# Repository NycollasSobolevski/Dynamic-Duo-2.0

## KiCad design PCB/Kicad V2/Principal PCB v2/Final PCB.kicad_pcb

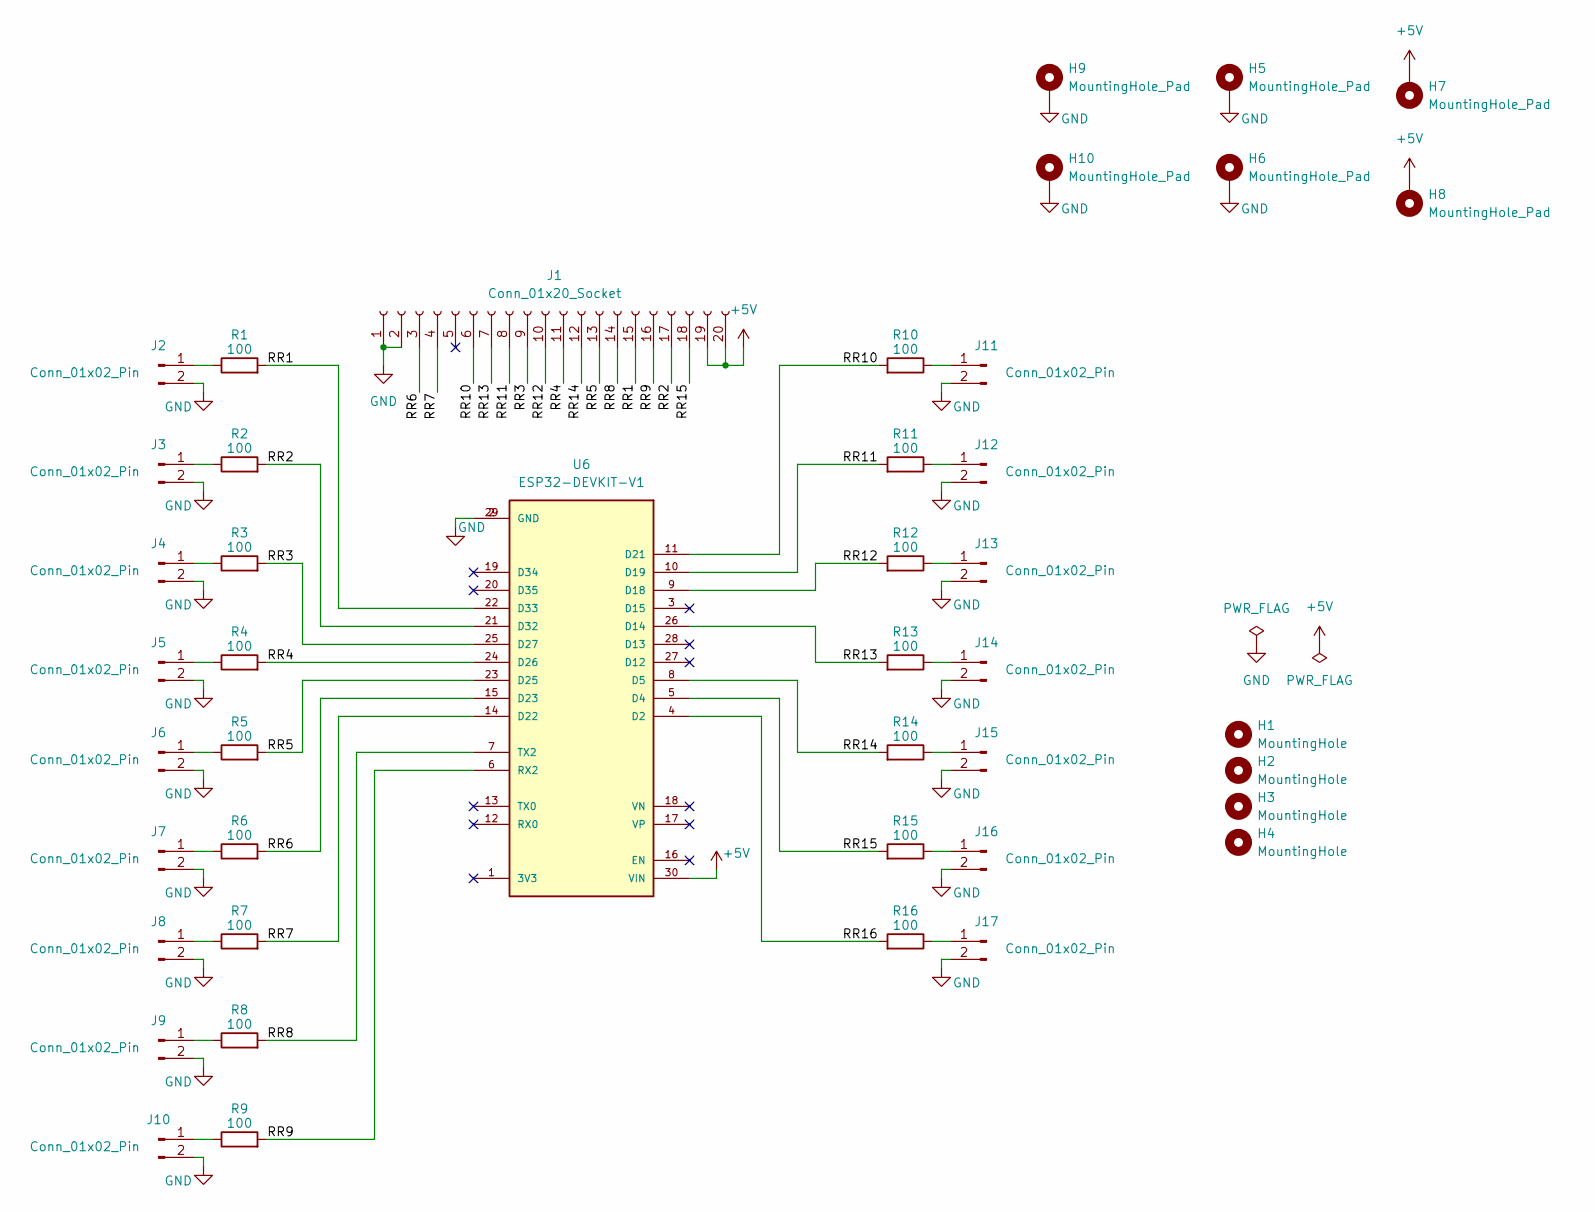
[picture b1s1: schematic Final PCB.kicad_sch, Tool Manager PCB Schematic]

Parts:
H1, H2, H3, H4: MountingHole; MountingHole_3.2mm_M3
H5, H6, H7, H8, H9, H10: MountingHole_Pad; DefaultVia
J1: Conn_01x20_Socket; PinSocket_2x10_P2.54mm_VerticalLongPads
J2, J3, J4, J5, J6, J7, J8, J9, J10, J11, J12, J13, J14, J15, J16, J17: Conn_01x02_Pin; PinHeader_1x02_P2.54mm_VerticalLongPads
R1, R2, R3, R4, R5, R6, R7, R8, R9, R10, R11, R12, R13, R14, R15, R16: 100; R_Axial_DIN0411_L9.9mm_D3.6mm_P12.70mm_HorizontalLONGPADS
U6: ESP32-DEVKIT-V1; MODULE_ESP32_DEVKIT_V1LongPads; PARTREV N/A

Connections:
+5V: H7.1, H8.1, J1.19, J1.20, U6.30 (VIN)
/RR1: J1.15, R1.2, U6.22 (D33)
/RR2: J1.17, R2.2, U6.21 (D32)
/RR3: J1.9, R3.2, U6.25 (D27)
/RR4: J1.11, R4.2, U6.24 (D26)
/RR5: J1.13, R5.2, U6.23 (D25)
/RR6: J1.3, R6.2, U6.15 (D23)
/RR7: J1.4, R7.2, U6.14 (D22)
/RR8: J1.14, R8.2, U6.7 (TX2)
/RR9: J1.16, R9.2, U6.6 (RX2)
/RR10: J1.6, R10.2, U6.11 (D21)
/RR11: J1.8, R11.2, U6.10 (D19)
/RR12: J1.10, R12.2, U6.9 (D18)
/RR13: J1.7, R13.2, U6.26 (D14)
/RR14: J1.12, R14.2, U6.8 (D5)
/RR15: J1.18, R15.2, U6.5 (D4)
/RR16: R16.2, U6.4 (D2)
GND: H5.1, H6.1, H9.1, H10.1, J1.1, J1.2, J2.2, J3.2, J4.2, J5.2, J6.2, J7.2, J8.2, J9.2, J10.2, J11.2, J12.2, J13.2, J14.2, J15.2, J16.2, J17.2, U6.2 (GND), U6.29 (GND)
unnamed: J2.1, R1.1
unnamed: J3.1, R2.1
unnamed: J4.1, R3.1
unnamed: J5.1, R4.1
unnamed: J6.1, R5.1
unnamed: J7.1, R6.1
unnamed: J8.1, R7.1
unnamed: J9.1, R8.1
unnamed: J10.1, R9.1
unnamed: J11.1, R10.1
unnamed: J12.1, R11.1
unnamed: J13.1, R12.1
unnamed: J14.1, R13.1
unnamed: J15.1, R14.1
unnamed: J16.1, R15.1
unnamed: J17.1, R16.1

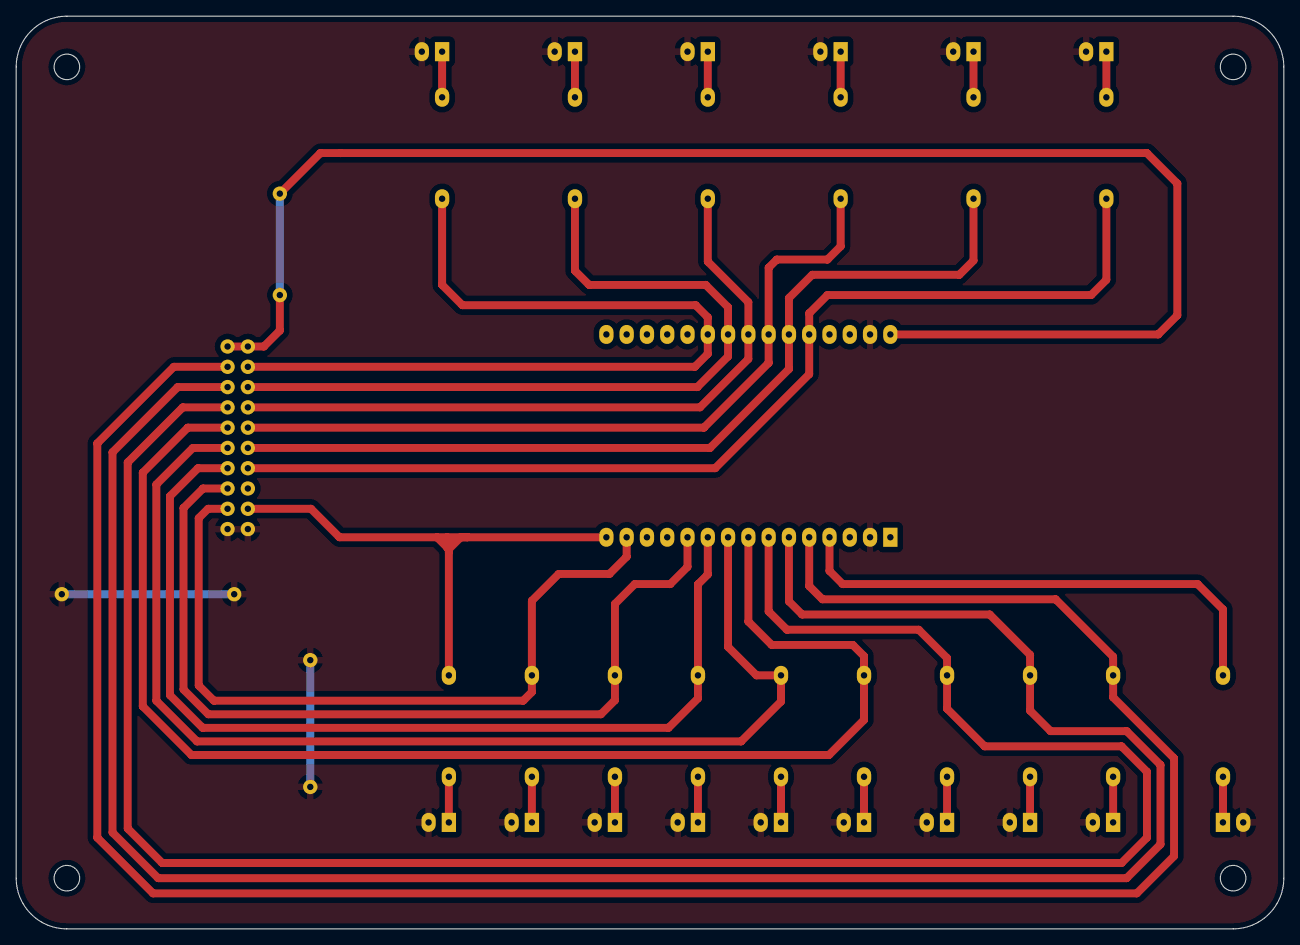
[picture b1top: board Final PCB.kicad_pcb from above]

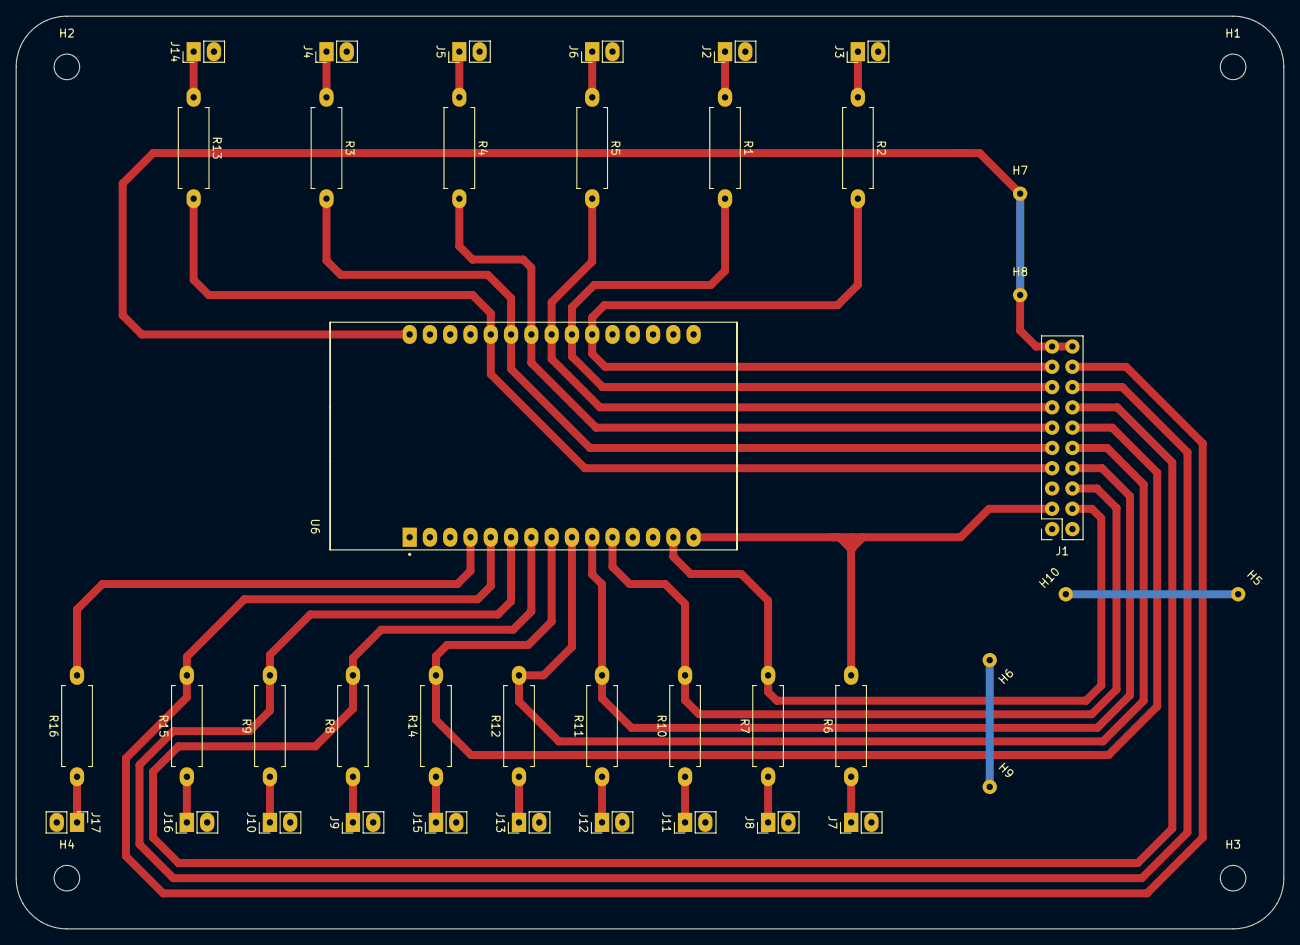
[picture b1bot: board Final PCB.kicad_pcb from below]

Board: 2 copper layers, 158.8 x 114.3 mm, 44 parts (44 on the bottom side), 34 nets.

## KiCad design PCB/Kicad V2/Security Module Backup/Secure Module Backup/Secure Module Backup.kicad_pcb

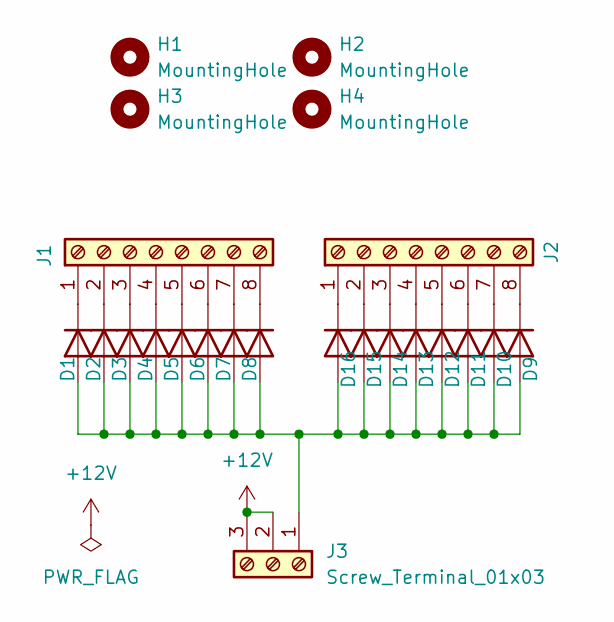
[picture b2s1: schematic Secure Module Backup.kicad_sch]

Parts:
D1, D2, D3, D4, D5, D6, D7, D8, D9, D10, D11, D12, D13, D14, D15, D16: D; D_5W_P10.16mm_Horizontal
H1, H2, H3, H4: MountingHole; MountingHole_3.2mm_M3
J1, J2: Screw_Terminal_01x08; TerminalBlock_Phoenix_MKDS-1,5-8-5.08_1x08_P5.08mm_Horizont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
J3: Screw_Terminal_01x03; TerminalBlock_Phoenix_MKDS-1,5-3-5.08_1x03_P5.08mm_Horizont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

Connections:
+12V: J3.2, J3.3
unnamed: D1.2 (A), D2.2 (A), D3.2 (A), D4.2 (A), D5.2 (A), D6.2 (A), D7.2 (A), D8.2 (A), D9.2 (A), D10.2 (A), D11.2 (A), D12.2 (A), D13.2 (A), D14.2 (A), D15.2 (A), D16.2 (A), J3.1
unnamed: D1.1 (K), J1.1
unnamed: D2.1 (K), J1.2
unnamed: D3.1 (K), J1.3
unnamed: D4.1 (K), J1.4
unnamed: D5.1 (K), J1.5
unnamed: D6.1 (K), J1.6
unnamed: D7.1 (K), J1.7
unnamed: D8.1 (K), J1.8
unnamed: D9.1 (K), J2.8
unnamed: D10.1 (K), J2.7
unnamed: D11.1 (K), J2.6
unnamed: D12.1 (K), J2.5
unnamed: D13.1 (K), J2.4
unnamed: D14.1 (K), J2.3
unnamed: D15.1 (K), J2.2
unnamed: D16.1 (K), J2.1

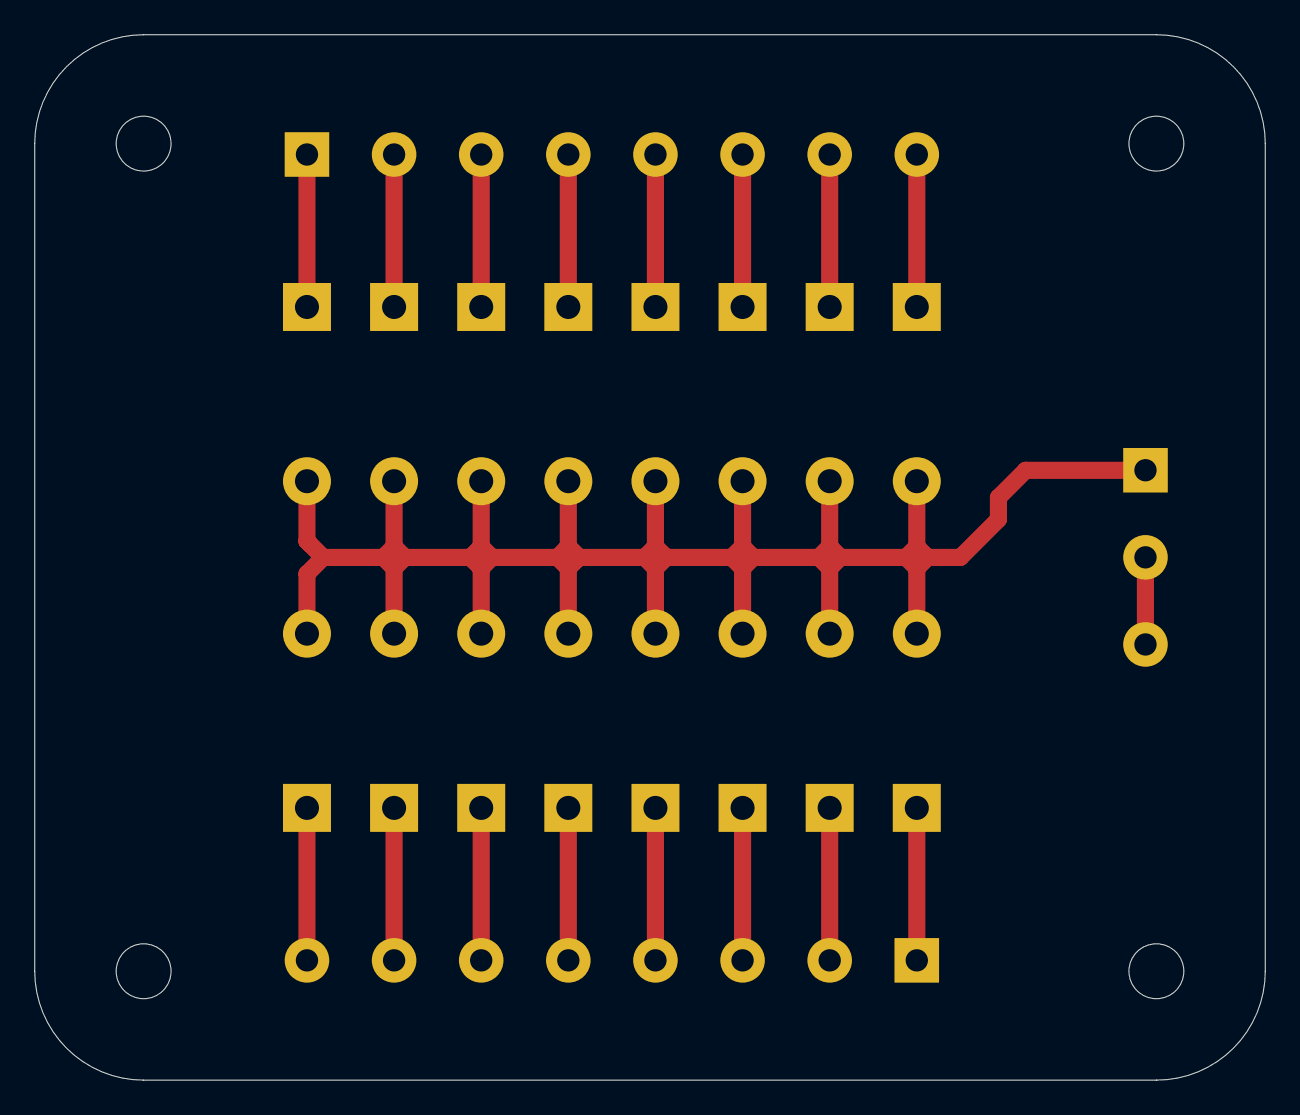
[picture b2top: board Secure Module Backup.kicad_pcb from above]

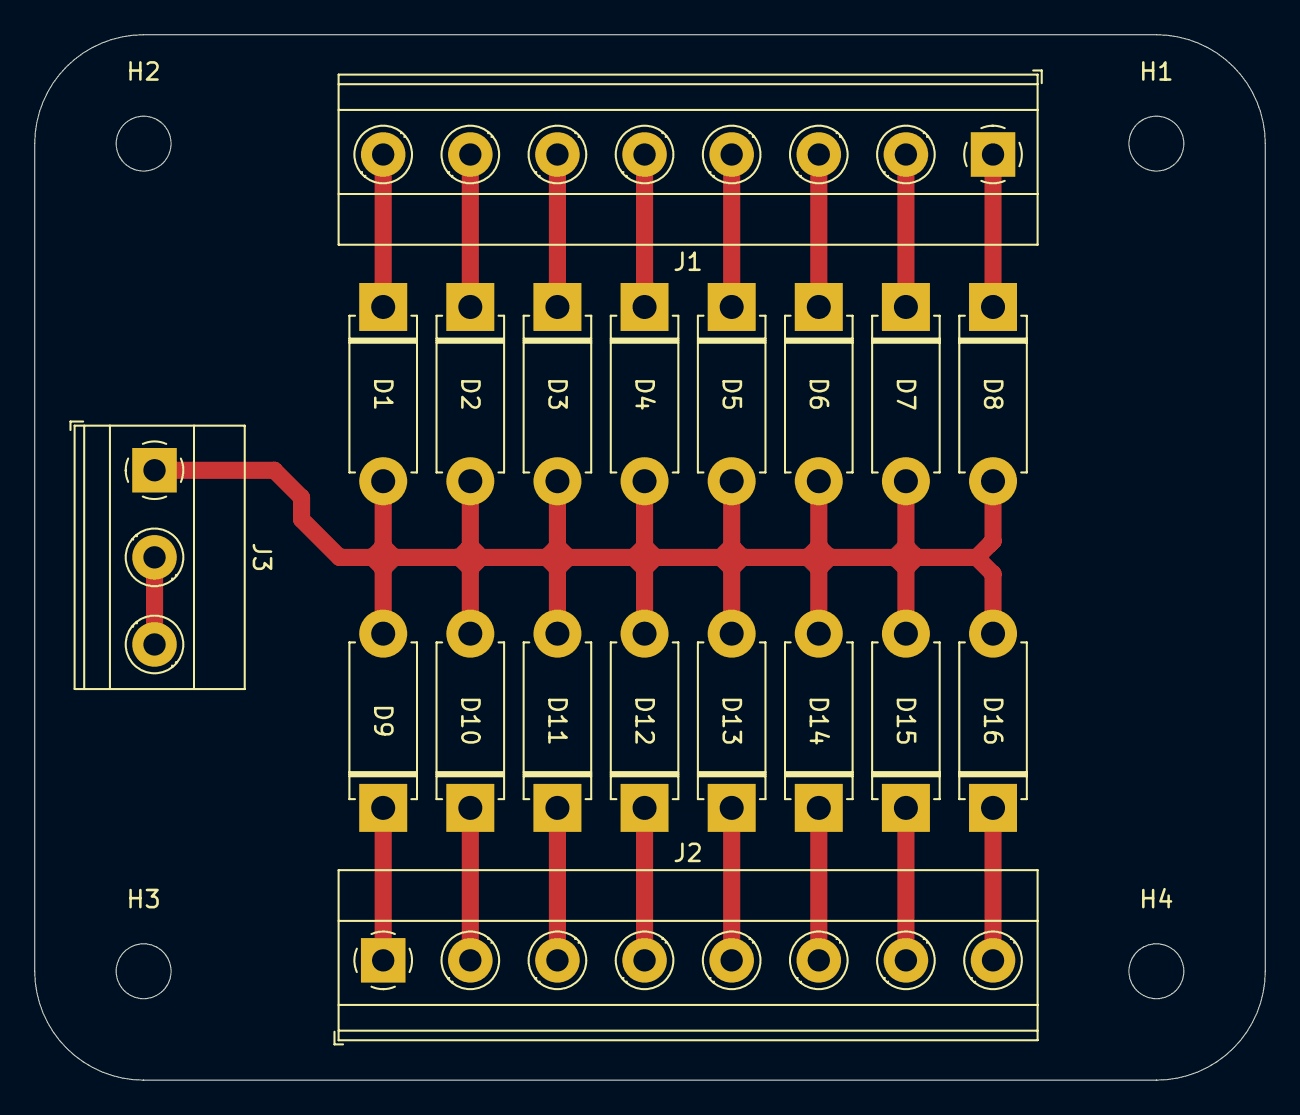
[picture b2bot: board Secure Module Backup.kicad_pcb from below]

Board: 2 copper layers, 71.8 x 61.0 mm, 23 parts (23 on the bottom side), 18 nets.

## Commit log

2024-09-05 REFATORED user action screen/modal
2024-09-05 Release 1.5.0
2024-10-07 Start refatored PCB
2024-10-08 REFATORE: PCB altered with no CI 4049
2024-10-08 UPDATE: PCB V2 ready
2024-10-09 UPDATE final pcb finished and ADD secure backup module
2024-10-09 ADD new uno code with calculate opened door with binnary
2024-10-10 UPDATE: esp32 code updated with binnary
2024-10-11 UPDATE: UI with send a number to firebase instead of object
2024-10-16 ADD Logs table structure
2024-10-29 UPDATE: getting tools by quantity
2024-10-29 UPDATE return tool by quantity
2024-10-29 UPDATE: disable btn by quantity
2024-10-29 FIX tool counter
2024-11-07 HOT FIX on prod
2024-11-07 FIX update item
2024-11-08 fix: update tools and see compartiment content
2024-11-08 fix: update tool
2024-12-16 fix start command with params
